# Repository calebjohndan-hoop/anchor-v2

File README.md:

# ANCHOR v2

**A two-ear noise cancelling earmuff for factory and construction workers that cancels machine noise but lets alarms and voices through.**

Status: design stage. v2 has not been built yet.

## What it is

ANCHOR is an industrial earmuff with active noise cancelling and a small on-device sound classifier. Microphones outside each cup hear the machine noise, and an ESP32-S3 plays anti-noise through a speaker inside the cup. When the classifier hears an alarm or a voice, ANCHOR stops cancelling and plays the outside sound into the ear instead.

## Why I'm making it

Earmuffs protect hearing but block everything, including reversing alarms, fire alarms and a supervisor shouting a warning. Many workers take them off to stay aware, which is when hearing gets damaged. Smart hearing protection that solves this exists, but it is expensive and imported. I want a low cost version that a factory in India could actually buy.

I already built a rough v1 (about ₹2,200) for a college design thinking course with my teammates. It proved the idea: noise cancelling works on steady machine hum, and the mic to speaker delay was 3.5 to 4.5 ms. But it was a breadboard with about 30 loose wires on the headband, one ear only, and ran from a power bank. v2 is a proper redesign. See [v1/README.md](v1/README.md).

## What changes in v2

| | v1 (built) | v2 (planned) |
|---|---|---|
| Ears with cancelling | 1 | 2 |
| Electronics | Breadboard on the headband | Custom PCBs inside the cups |
| Wiring | About 30 jumper wires | One 8-wire cable, digital signals only |
| Power | USB power bank | 1000 mAh LiPo, USB-C charging |
| Mic to speaker delay | 3.5 to 4.5 ms (measured) | Under 1 ms (target) |
| Noise reduction | Not measured | Measured with a sound level meter |

## Firmware and AI

v2 keeps the v1 firmware and the trained sound classifier. Each ear is wired exactly like v1 on its own I2S port (left ear on the v1 pins), so v1 sketches run on the left ear unchanged, and [firmware/v2/11_anchor_v2](firmware/v2/11_anchor_v2) runs the v1 cancelling engine in both ears with the same AI. It compiles and links for the ESP32-S3 with both the built-in AI and the Edge Impulse model; it has not run on v2 hardware yet. The ICS-43434 mics have the same -26 dBFS sensitivity and 24-bit I2S format as v1's INMP441, so the training clips still match.

## Design

Full plan: [docs/DESIGN.md](docs/DESIGN.md)

### Wiring

### Schematic and PCB

Three KiCad 7 boards: the main board (51 x 38 mm, left cup), a mic board (12 x 13 mm, four needed) and a right cup hub (30 x 22 mm). Schematics, layouts, Gerbers and JLCPCB BOM and position files are in [pcb/](pcb/).

**Status:** routed and DRC clean (no clearance, unconnected or courtyard errors), but this is a first revision that has **not been reviewed by a second person or built**. See [pcb/README.md](pcb/README.md) for the checks to do before ordering.

### 3D model

Enclosure parts are parametric CadQuery models ([cad/anchor_cad.py](cad/anchor_cad.py)) with STEP files, also imported into [Onshape](https://cad.onshape.com/documents/01ac43861da2c203e8e859be). Cup sizes are placeholders until the earmuff is measured.

## Repo layout

| Folder | Contents |
|---|---|
| `docs/` | Design plan and diagrams |
| `pcb/` | KiCad projects: main board, mic board, right hub |
| `cad/` | Onshape link and exported STEP and STL files |
| `firmware/` | ESP32-S3 Arduino code |
| `v1/` | Photos and notes from the first prototype |

## Credits

v1 was built with my college teammates. I used Claude (an AI assistant) to write this v2 design plan, generate the CAD models and lay out the PCBs. I am reviewing them before anything is ordered.

## Bill of materials

Everything comes in two online orders, delivered: one JLCPCB order (boards fully assembled, chips, and the 3D printed parts) and one Amazon.in order (earmuff, battery, speakers, cables, fixings, tools). Prices are estimates without shipping and will be replaced with the real cart prices before review. Full list with notes: [BOM.csv](BOM.csv).

| Part | Qty | Unit (USD) | Total (USD) | Vendor | Funding |
|---|---|---|---|---|---|
| [PCB fabrication: main, hub, mic boards](https://jlcpcb.com/) | 1 | 10.00 | 10.00 | JLCPCB | Requested |
| [PCB assembly (4 jobs: main, hub, mic REF, mic ERR)](https://jlcpcb.com/) | 1 | 70.00 | 70.00 | JLCPCB | Requested |
| [ESP32-S3-WROOM-1-N16R8 module](https://www.lcsc.com/product-detail/C2913202.html) | 2 | 5.50 | 11.00 | JLCPCB | Requested |
| [MAX98357AETE+T I2S class D amplifier](https://www.lcsc.com/product-image/C910544.html) | 4 | 2.00 | 8.00 | JLCPCB | Requested |
| [ICS-43434 I2S MEMS microphone](https://www.lcsc.com/product-detail/C5656610.html) | 10 | 2.50 | 25.00 | JLCPCB | Requested |
| [MCP73831T-2ACI/OT LiPo charger IC](https://www.lcsc.com/search?q=MCP73831T-2ACI%2FOT) | 2 | 0.60 | 1.20 | JLCPCB | Requested |
| [AP2112K-3.3 LDO regulator](https://www.lcsc.com/search?q=AP2112K-3.3TRG1) | 2 | 0.20 | 0.40 | JLCPCB | Requested |
| [USBLC6-2SC6 USB ESD protection](https://www.lcsc.com/search?q=USBLC6-2SC6) | 2 | 0.20 | 0.40 | JLCPCB | Requested |
| [USB-C 16-pin receptacle](https://www.lcsc.com/search?q=TYPE-C%2016PIN) | 2 | 0.30 | 0.60 | JLCPCB | Requested |
| [AO3401A P-MOSFETs + SS14 Schottky](https://www.lcsc.com/search?q=AO3401A) | 4 | 0.20 | 0.80 | JLCPCB | Requested |
| [JST-SH and JST-PH SMD connectors](https://www.lcsc.com/search?q=SM05B-SRSS-TB) | 28 | 0.15 | 4.20 | JLCPCB | Requested |
| [Passives lot (resistors, capacitors, ferrite bead)](https://www.lcsc.com/search?q=0603%20resistor) | 1 | 4.00 | 4.00 | JLCPCB | Requested |
| [Buttons, slide switch, LEDs](https://www.lcsc.com/search?q=tactile%20switch) | 1 | 2.00 | 2.00 | JLCPCB | Requested |
| [3D printed enclosure parts (JLC3DP, resin)](https://jlc3dp.com/) | 1 | 30.00 | 30.00 | JLCPCB | Requested |
| [Industrial safety earmuff (same model as v1)](https://www.amazon.in/s?k=industrial+safety+earmuff+red) | 1 | 5.00 | 5.00 | Amazon.in | Requested |
| [3.7 V 1000 mAh LiPo (503450) with JST-PH plug](https://www.amazon.in/s?k=3.7v+1000mah+lipo+battery+503450+jst+ph) | 2 | 5.00 | 10.00 | Amazon.in | Requested |
| [40 mm 32 ohm headphone driver](https://www.amazon.in/s?k=40mm+32+ohm+headphone+driver) | 4 | 4.00 | 16.00 | Amazon.in | Requested |
| [JST-SH 1.0 mm double-ended cables (2, 5 and 8 pin)](https://www.amazon.in/s?k=JST+SH+1.0mm+double+ended+cable) | 1 | 8.00 | 8.00 | Amazon.in | Requested |
| [M2 screw assortment](https://www.amazon.in/s?k=M2+screw+assortment+kit) | 1 | 4.00 | 4.00 | Amazon.in | Requested |
| [Acoustic foam sheet](https://www.amazon.in/s?k=acoustic+foam+sheet+thin) | 1 | 4.00 | 4.00 | Amazon.in | Requested |
| [Double-sided foam tape](https://www.amazon.in/s?k=double+sided+foam+tape) | 1 | 3.00 | 3.00 | Amazon.in | Requested |
| [Heat shrink and spiral cable wrap](https://www.amazon.in/s?k=heat+shrink+tube+kit) | 1 | 4.00 | 4.00 | Amazon.in | Requested |
| [UNI-T UT353 sound level meter](https://www.amazon.in/s?k=UNI-T+UT353+sound+level+meter) | 1 | 27.00 | 27.00 | Amazon.in | Requested |
| [Soldering iron kit with multimeter, solder and flux](https://www.amazon.in/s?k=soldering+iron+kit+with+multimeter) | 1 | 27.00 | 27.00 | Amazon.in | Requested |
| **Total** |  |  | **275.60** |  |  |
| **Grant total** |  |  | **275.60** |  |  |

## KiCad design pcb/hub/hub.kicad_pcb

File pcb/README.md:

# PCBs (KiCad 7)

| Board | Size | Qty | Folder |
|---|---|---|---|
| Main board (left cup): ESP32-S3-WROOM-1-N16R8, left MAX98357A, MCP73831 charger, AP2112K-3.3, USB-C | 51 x 38 mm | 1 per headset | [main/](main/) |
| Mic board: ICS-43434, JST-SH 5, sound port hole; REF and ERR builds | 12 x 13 mm | 2 REF + 2 ERR per headset | [mic/](mic/) |
| Right cup hub: right MAX98357A, 8-pin cable in, 2 mic sockets, speaker socket | 30 x 22 mm | 1 per headset | [hub/](hub/) |

Each folder has the schematic (`.kicad_sch`, plus a PDF), the board (`.kicad_pcb`), the DRC report, front and back images, and `fab/` with Gerbers, drill files, `positions.csv` and `bom-jlcpcb.csv` for assembly.

## How these were made

The boards are generated from code in [gen/](gen/): `boards.py` lists every part and connection, `place.py` sets the placement, and `run_all.py` builds the schematics and boards, routes them with Freerouting, adds ground pours, runs DRC and exports the fab files. KiCad reads the schematics back and the script checks every net matches the parts list.

Schematics are drawn with net labels (parts joined by labels with the same name) rather than wires.

## DRC status

All three boards: no clearance, unconnected, short or courtyard errors. Remaining items are silkscreen text overlaps (cosmetic) and "footprint not in project library" notices, because the boards use KiCad's standard libraries.

## Design notes

- **Radio is not used.** The ESP32-S3 antenna keepout and its large courtyard were removed so parts and ground pour can sit near the module. If Wi-Fi or Bluetooth is ever needed, the board must be re-laid out with the keepout back.
- **Mic boards: one PCB, two builds.** The REF build fits R1 (L/R to GND, left slot) and the ERR build fits R2 (L/R to 3.3 V, right slot), exactly like v1's INMP441 wiring. Order the mic PCB twice at JLCPCB, once with `fab/bom-jlcpcb-REF.csv` and once with `fab/bom-jlcpcb-ERR.csv`. Nothing to bridge by hand.
- **Mic GND ring:** the ICS-43434 GND pad is a ring around the sound port; a short trace was added by hand because the autorouter skips that pad shape. Loose copper rings in the library footprint were removed.
- **Charge status:** MCP73831 STAT swings to 5 V, so it reaches GPIO 2 through a 10k/20k divider.
- **Each ear is its own I2S port, wired like v1:** left on GPIO 5, 6, 7, 15 (v1 pins), right on GPIO 17, 18, 21, 16. Both amps get SD_MODE through 10 kΩ from GPIO 8, which has a 10 kΩ pull-up, so the amps are on by default and v1 firmware works without changes. The firmware writes the same sound to both slots, as in v1.
- **Speakers** connect with 2-pin JST-SH, the battery with 2-pin JST-PH (most LiPo packs come with PH).
- **Right amp on the hub:** the headband cable carries only the right ear's digital I2S port (pin 1 to 8: 3V3, GND, BCLK, WS, DIN, GND, DOUT, AMP_SD). Class D speaker outputs never run beside the mic lines. The hub amp runs from 3.3 V through a ferrite bead.
- **Reverse battery protection:** AO3401A P-MOSFET in the battery line (gate to GND).
- **Power switch** drives only the regulator EN pin (100 kΩ pull-down), so its 300 mA rating is not an issue.
- **Cable:** the 8-pin JST-SH cable must be wired pin 1 to pin 1. Pre-made SH cables are sold both straight and reversed; check before plugging in.

## Check before ordering

This is an autorouted first revision and has not been built.

- [ ] Open each board in KiCad 7 or 8 and run DRC and ERC yourself
- [ ] Check the ICS-43434 footprint and sound port against the TDK datasheet
- [ ] Check the MAX98357A SD_MODE voltage window for "left/both" (about 2.5 V here) in the datasheet
- [ ] Look over the autorouted traces and add GND stitching vias if the pours look broken up
- [ ] Run ERC in KiCad (the command-line KiCad 7 used here cannot)
- [ ] Check the battery's plug polarity matches J2 (pin 1 = +) before connecting; the MOSFET protects against a reversed pack, but check anyway
- [ ] Confirm every part in `bom-jlcpcb.csv` is in stock at JLCPCB, then fill in the LCSC part numbers
- [ ] Measure the earmuff and confirm the board outlines fit the cup trays in [../cad/](../cad/)

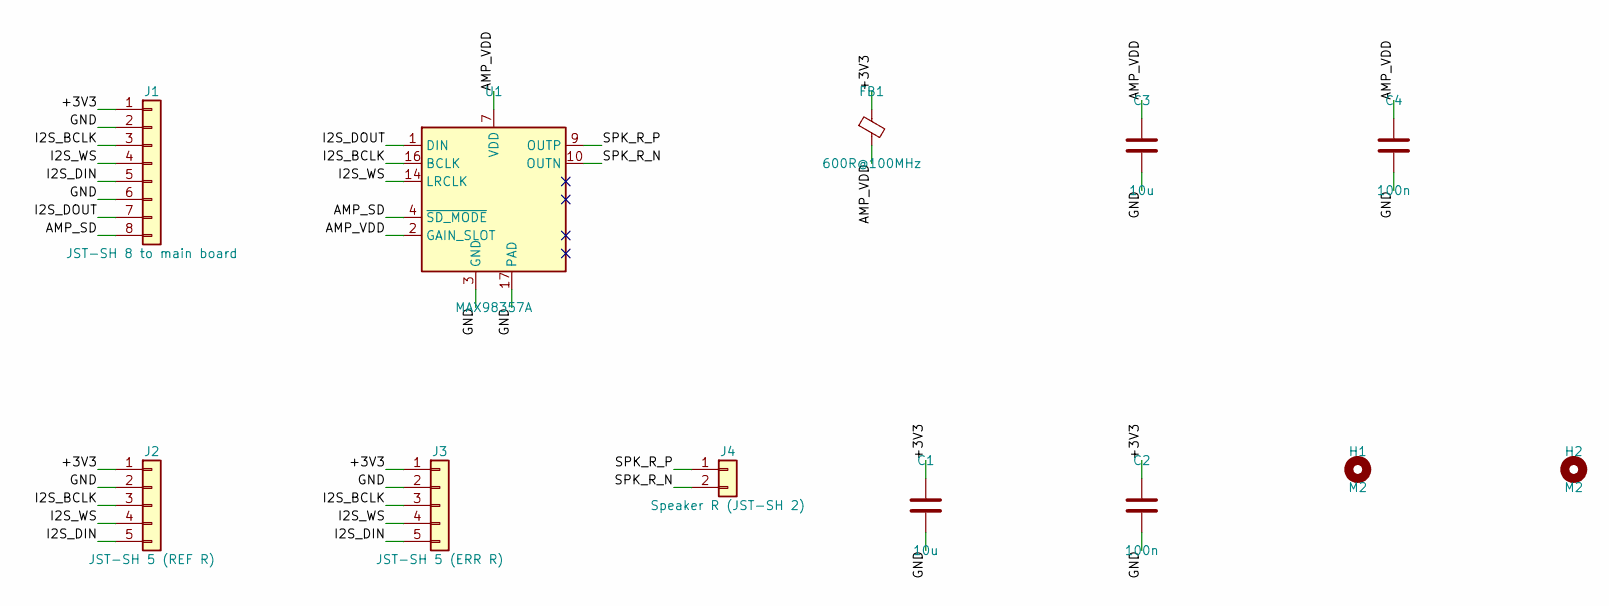
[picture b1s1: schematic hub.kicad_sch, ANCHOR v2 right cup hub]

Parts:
C1, C3: 10u; C_0805_2012Metric
C2, C4: 100n; C_0603_1608Metric
FB1: 600R@100MHz; L_0603_1608Metric
H1, H2: M2; MountingHole_2.2mm_M2
J1: JST-SH 8 to main board; JST_SH_SM08B-SRSS-TB_1x08-1MP_P1.00mm_Horizontal; MPN SM08B-SRSS-TB
J2: JST-SH 5 (REF R); JST_SH_SM05B-SRSS-TB_1x05-1MP_P1.00mm_Horizontal; MPN SM05B-SRSS-TB
J3: JST-SH 5 (ERR R); JST_SH_SM05B-SRSS-TB_1x05-1MP_P1.00mm_Horizontal; MPN SM05B-SRSS-TB
J4: Speaker R (JST-SH 2); JST_SH_SM02B-SRSS-TB_1x02-1MP_P1.00mm_Horizontal; MPN SM02B-SRSS-TB
U1: MAX98357A; TQFN-16-1EP_3x3mm_P0.5mm_EP1.23x1.23mm; MPN MAX98357AETE+T; LCSC C910544

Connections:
+3V3: C1.1, C2.1, FB1.1, J1.1, J2.1, J3.1
AMP_SD: J1.8, U1.4 (~SD_MODE)
AMP_VDD: C3.1, C4.1, FB1.2, U1.2 (GAIN_SLOT), U1.7 (VDD), U1.8 (VDD)
GND: C1.2, C2.2, C3.2, C4.2, J1.2, J1.6, J2.2, J3.2, U1.3 (GND), U1.11 (GND), U1.15 (GND), U1.17 (PAD)
I2S_BCLK: J1.3, J2.3, J3.3, U1.16 (BCLK)
I2S_DIN: J1.5, J2.5, J3.5
I2S_DOUT: J1.7, U1.1 (DIN)
I2S_WS: J1.4, J2.4, J3.4, U1.14 (LRCLK)
SPK_R_N: J4.2, U1.10 (OUTN)
SPK_R_P: J4.1, U1.9 (OUTP)

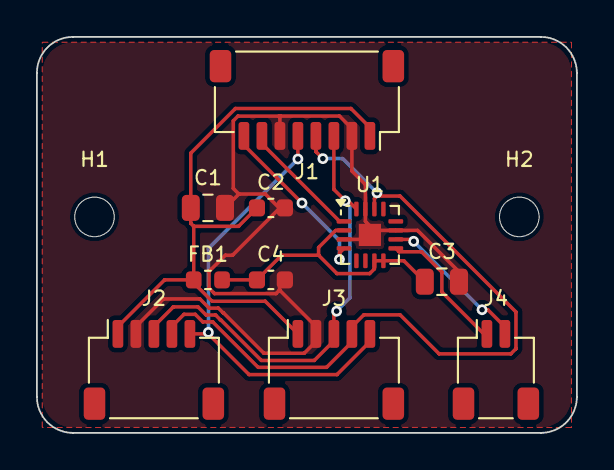
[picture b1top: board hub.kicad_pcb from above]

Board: 2 copper layers, 30.0 x 22.0 mm, 12 parts (0 on the bottom side), 10 nets.

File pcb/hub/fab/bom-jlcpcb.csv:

Comment,Designator,Footprint,LCSC Part #,MPN
10u,"C3,C1",C_0805_2012Metric,,
100n,"C4,C2",C_0603_1608Metric,,
600R@100MHz,FB1,L_0603_1608Metric,,
JST-SH 8 to main board,J1,JST_SH_SM08B-SRSS-TB_1x08-1MP_P1.00mm_Horizontal,,SM08B-SRSS-TB
JST-SH 5 (REF R),J2,JST_SH_SM05B-SRSS-TB_1x05-1MP_P1.00mm_Horizontal,,SM05B-SRSS-TB
JST-SH 5 (ERR R),J3,JST_SH_SM05B-SRSS-TB_1x05-1MP_P1.00mm_Horizontal,,SM05B-SRSS-TB
Speaker R (JST-SH 2),J4,JST_SH_SM02B-SRSS-TB_1x02-1MP_P1.00mm_Horizontal,,SM02B-SRSS-TB
MAX98357A,U1,TQFN-16-1EP_3x3mm_P0.5mm_EP1.23x1.23mm,C910544,MAX98357AETE+T

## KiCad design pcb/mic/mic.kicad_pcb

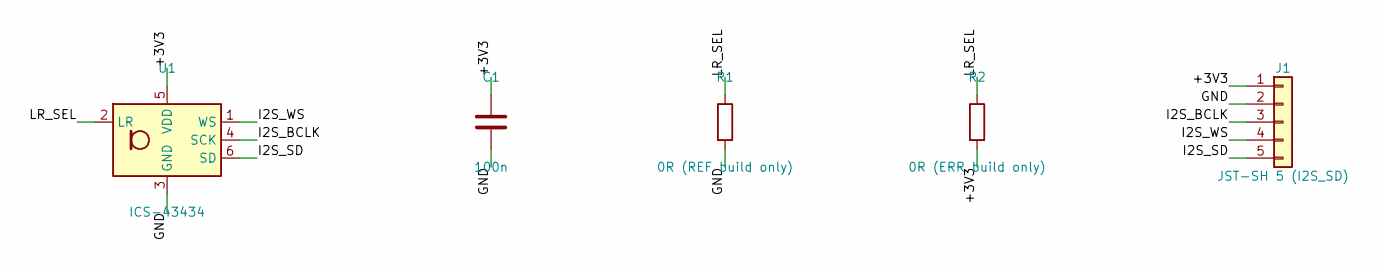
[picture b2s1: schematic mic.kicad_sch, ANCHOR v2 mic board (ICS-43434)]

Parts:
C1: 100n; C_0603_1608Metric
J1: JST-SH 5 (I2S_SD); JST_SH_SM05B-SRSS-TB_1x05-1MP_P1.00mm_Horizontal; MPN SM05B-SRSS-TB
R1: 0R (REF build only); R_0603_1608Metric
R2: 0R (ERR build only); R_0603_1608Metric
U1: ICS-43434; InvenSense_ICS-43434-6_3.5x2.65mm; MPN ICS-43434; LCSC C5656610

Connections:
+3V3: C1.1, J1.1, R2.2, U1.5 (VDD)
GND: C1.2, J1.2, R1.2, U1.3 (GND)
I2S_BCLK: J1.3, U1.4 (SCK)
I2S_SD: J1.5, U1.6 (SD)
I2S_WS: J1.4, U1.1 (WS)
LR_SEL: R1.1, R2.1, U1.2 (LR)

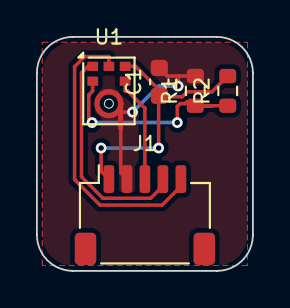
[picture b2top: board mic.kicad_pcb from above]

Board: 2 copper layers, 12.0 x 13.0 mm, 5 parts (0 on the bottom side), 6 nets.

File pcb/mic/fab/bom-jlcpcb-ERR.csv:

Comment,Designator,Footprint,LCSC Part #,MPN
100n,C1,C_0603_1608Metric,,
JST-SH 5 (I2S_SD),J1,JST_SH_SM05B-SRSS-TB_1x05-1MP_P1.00mm_Horizontal,,SM05B-SRSS-TB
0R,R2,R_0603_1608Metric,,
ICS-43434,U1,InvenSense_ICS-43434-6_3.5x2.65mm,C5656610,ICS-43434

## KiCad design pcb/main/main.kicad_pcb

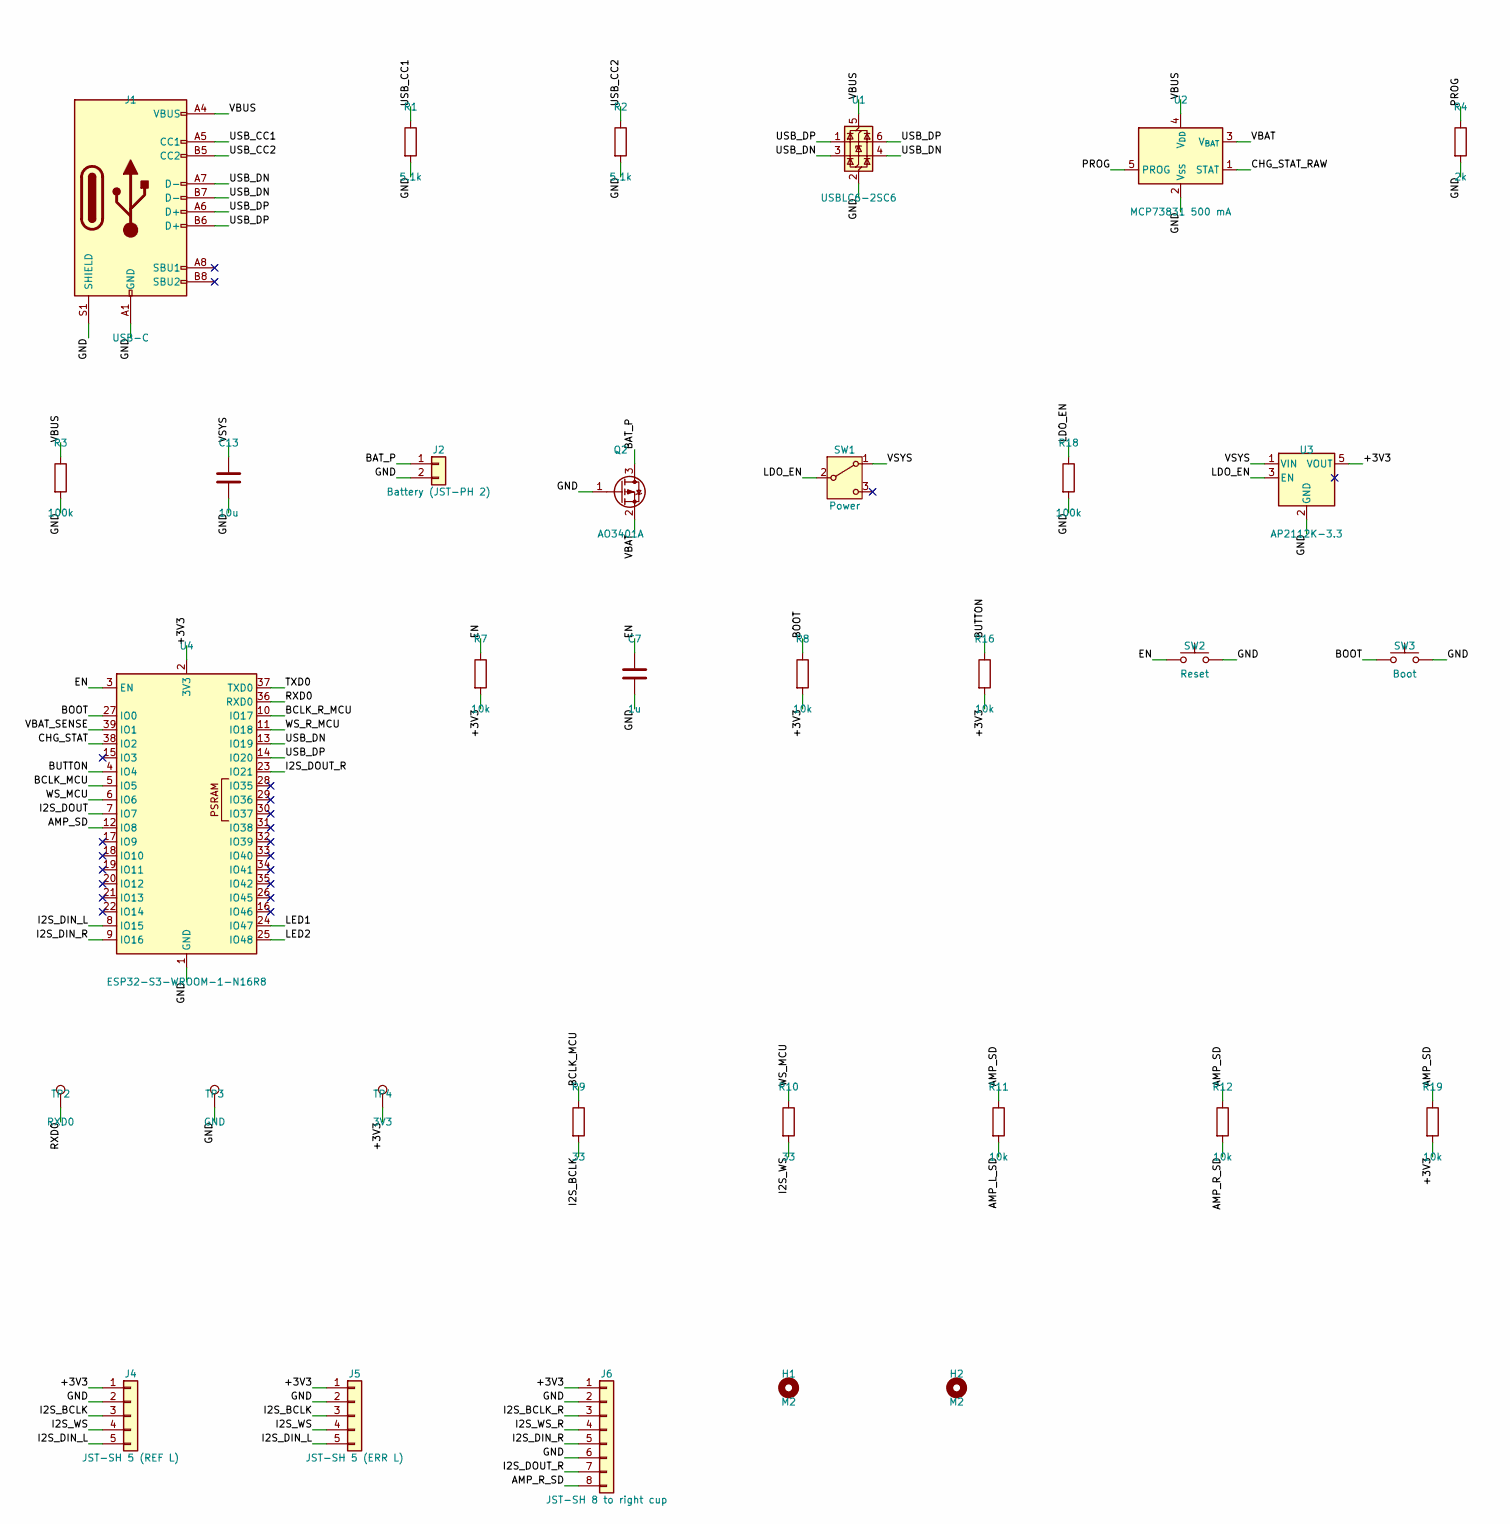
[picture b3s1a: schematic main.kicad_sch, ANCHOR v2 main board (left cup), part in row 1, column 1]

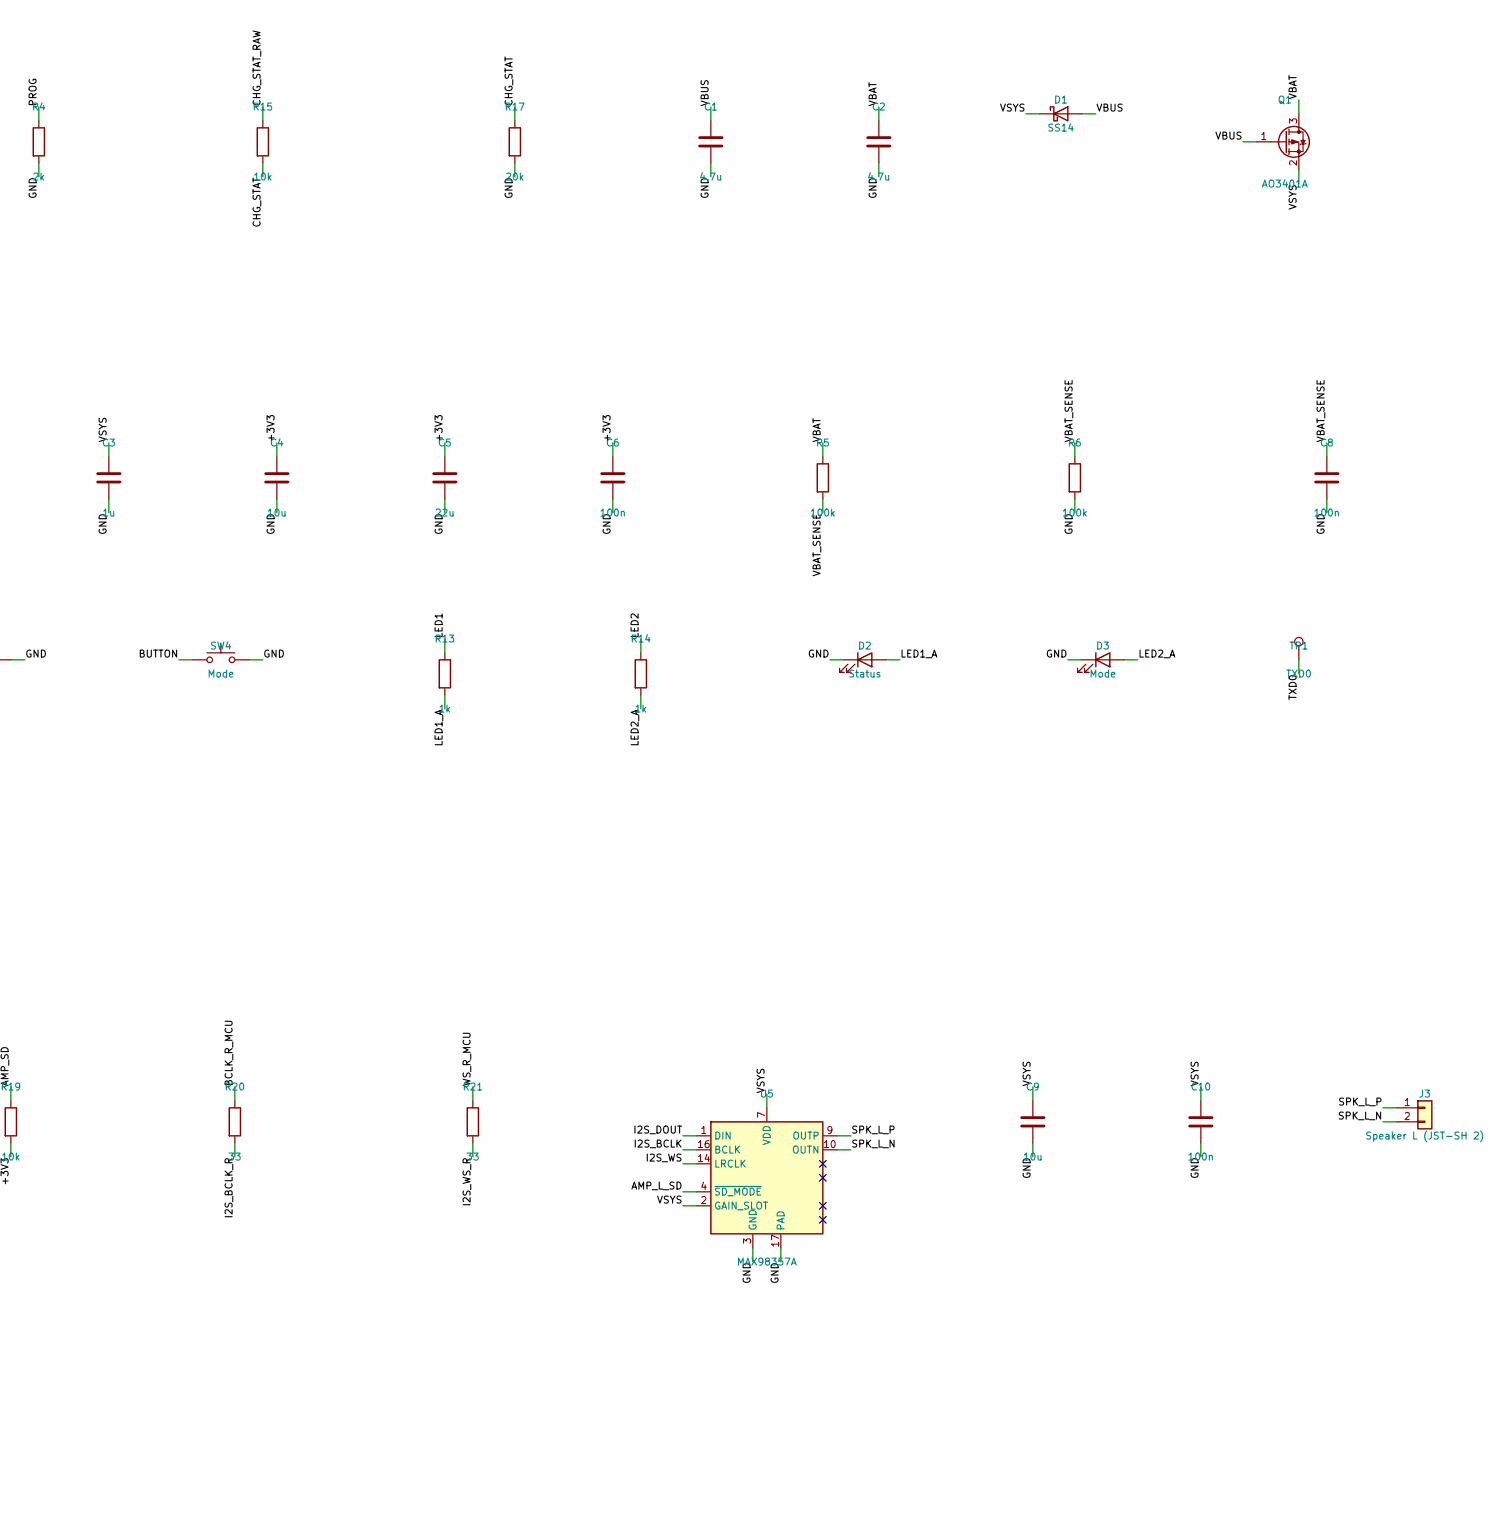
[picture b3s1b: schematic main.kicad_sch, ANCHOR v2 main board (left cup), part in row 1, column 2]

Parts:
C1, C2: 4.7u; C_0603_1608Metric
C3, C7: 1u; C_0603_1608Metric
C4, C9, C13: 10u; C_0805_2012Metric
C5: 22u; C_0805_2012Metric
C6, C8, C10: 100n; C_0603_1608Metric
D1: SS14; D_SMA; MPN SS14
D2: Status; LED_0603_1608Metric
D3: Mode; LED_0603_1608Metric
H1, H2: M2; MountingHole_2.2mm_M2
J1: USB-C; USB_C_Receptacle_HRO_TYPE-C-31-M-12; MPN TYPE-C-31-M-12
J2: Battery (JST-PH 2); JST_PH_S2B-PH-SM4-TB_1x02-1MP_P2.00mm_Horizontal; MPN S2B-PH-SM4-TB
J3: Speaker L (JST-SH 2); JST_SH_SM02B-SRSS-TB_1x02-1MP_P1.00mm_Horizontal; MPN SM02B-SRSS-TB
J4: JST-SH 5 (REF L); JST_SH_SM05B-SRSS-TB_1x05-1MP_P1.00mm_Horizontal; MPN SM05B-SRSS-TB
J5: JST-SH 5 (ERR L); JST_SH_SM05B-SRSS-TB_1x05-1MP_P1.00mm_Horizontal; MPN SM05B-SRSS-TB
J6: JST-SH 8 to right cup; JST_SH_SM08B-SRSS-TB_1x08-1MP_P1.00mm_Horizontal; MPN SM08B-SRSS-TB
Q1, Q2: AO3401A; SOT-23; MPN AO3401A
R1, R2: 5.1k; R_0603_1608Metric
R3, R5, R6, R18: 100k; R_0603_1608Metric
R4: 2k; R_0603_1608Metric
R7, R8, R11, R12, R15, R16, R19: 10k; R_0603_1608Metric
R9, R10, R20, R21: 33; R_0603_1608Metric
R13, R14: 1k; R_0603_1608Metric
R17: 20k; R_0603_1608Metric
SW1: Power; SW_SPDT_PCM12; MPN PCM12SMTR
SW2: Reset; SW_Push_1P1T_NO_CK_KMR2
SW3: Boot; SW_Push_1P1T_NO_CK_KMR2
SW4: Mode; SW_Push_1P1T_NO_CK_KMR2
TP1: TXD0; TestPoint_Pad_D1.0mm
TP2: RXD0; TestPoint_Pad_D1.0mm
TP3: GND; TestPoint_Pad_D1.0mm
TP4: 3V3; TestPoint_Pad_D1.0mm
U1: USBLC6-2SC6; SOT-23-6; MPN USBLC6-2SC6
U2: MCP73831 500 mA; SOT-23-5; MPN MCP73831T-2ACI/OT
U3: AP2112K-3.3; SOT-23-5; MPN AP2112K-3.3TRG1
U4: ESP32-S3-WROOM-1-N16R8; ESP32-S3-WROOM-1; MPN ESP32-S3-WROOM-1-N16R8; LCSC C2913202
U5: MAX98357A; TQFN-16-1EP_3x3mm_P0.5mm_EP1.23x1.23mm; MPN MAX98357AETE+T; LCSC C910544

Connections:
+3V3: C4.1, C5.1, C6.1, J4.1, J5.1, J6.1, R7.2, R8.2, R16.2, R19.2, TP4.1, U3.5 (VOUT), U4.2 (3V3)
AMP_L_SD: R11.2, U5.4 (~SD_MODE)
AMP_R_SD: J6.8, R12.2
AMP_SD: R11.1, R12.1, R19.1, U4.12 (IO8)
BAT_P: J2.1, Q2.3 (D)
BCLK_MCU: R9.1, U4.5 (IO5)
BCLK_R_MCU: R20.1, U4.10 (IO17)
BOOT: R8.1, SW3.1, U4.27 (IO0)
BUTTON: R16.1, SW4.1, U4.4 (IO4)
CHG_STAT: R15.2, R17.1, U4.38 (IO2)
CHG_STAT_RAW: R15.1, U2.1 (STAT)
EN: C7.1, R7.1, SW2.1, U4.3 (EN)
GND: C1.2, C2.2, C3.2, C4.2, C5.2, C6.2, C7.2, C8.2, C9.2, C10.2, C13.2, D2.1 (K), D3.1 (K), J1.A1 (GND), J1.A12 (GND), J1.B1 (GND), J1.B12 (GND), J1.S1 (SHIELD), J2.2, J4.2, J5.2, J6.2, J6.6, Q2.1 (G), R1.2, R2.2, R3.2, R4.2, R6.2, R17.2, R18.2, SW2.2, SW3.2, SW4.2, TP3.1, U1.2 (GND), U2.2 (V_{SS}), U3.2 (GND), U4.1 (GND), U4.40 (GND), U4.41 (GND), U5.3 (GND), U5.11 (GND), U5.15 (GND), U5.17 (PAD)
I2S_BCLK: J4.3, J5.3, R9.2, U5.16 (BCLK)
I2S_BCLK_R: J6.3, R20.2
I2S_DIN_L: J4.5, J5.5, U4.8 (IO15)
I2S_DIN_R: J6.5, U4.9 (IO16)
I2S_DOUT: U4.7 (IO7), U5.1 (DIN)
I2S_DOUT_R: J6.7, U4.23 (IO21)
I2S_WS: J4.4, J5.4, R10.2, U5.14 (LRCLK)
I2S_WS_R: J6.4, R21.2
LDO_EN: R18.1, SW1.2 (B), U3.3 (EN)
LED1: R13.1, U4.24 (IO47)
LED1_A: D2.2 (A), R13.2
LED2: R14.1, U4.25 (IO48)
LED2_A: D3.2 (A), R14.2
PROG: R4.1, U2.5 (PROG)
RXD0: TP2.1, U4.36 (RXD0)
SPK_L_N: J3.2, U5.10 (OUTN)
SPK_L_P: J3.1, U5.9 (OUTP)
TXD0: TP1.1, U4.37 (TXD0)
USB_CC1: J1.A5 (CC1), R1.1
USB_CC2: J1.B5 (CC2), R2.1
USB_DN: J1.A7 (D-), J1.B7 (D-), U1.3 (I/O2), U1.4 (I/O2), U4.13 (IO19)
USB_DP: J1.A6 (D+), J1.B6 (D+), U1.1 (I/O1), U1.6 (I/O1), U4.14 (IO20)
VBAT: C2.1, Q1.3 (D), Q2.2 (S), R5.1, U2.3 (V_{BAT})
VBAT_SENSE: C8.1, R5.2, R6.1, U4.39 (IO1)
VBUS: C1.1, D1.2 (A), J1.A4 (VBUS), J1.A9 (VBUS), J1.B4 (VBUS), J1.B9 (VBUS), Q1.1 (G), R3.1, U1.5 (VBUS), U2.4 (V_{DD})
VSYS: C3.1, C9.1, C10.1, C13.1, D1.1 (K), Q1.2 (S), SW1.1 (A), U3.1 (VIN), U5.2 (GAIN_SLOT), U5.7 (VDD), U5.8 (VDD)
WS_MCU: R10.1, U4.6 (IO6)
WS_R_MCU: R21.1, U4.11 (IO18)

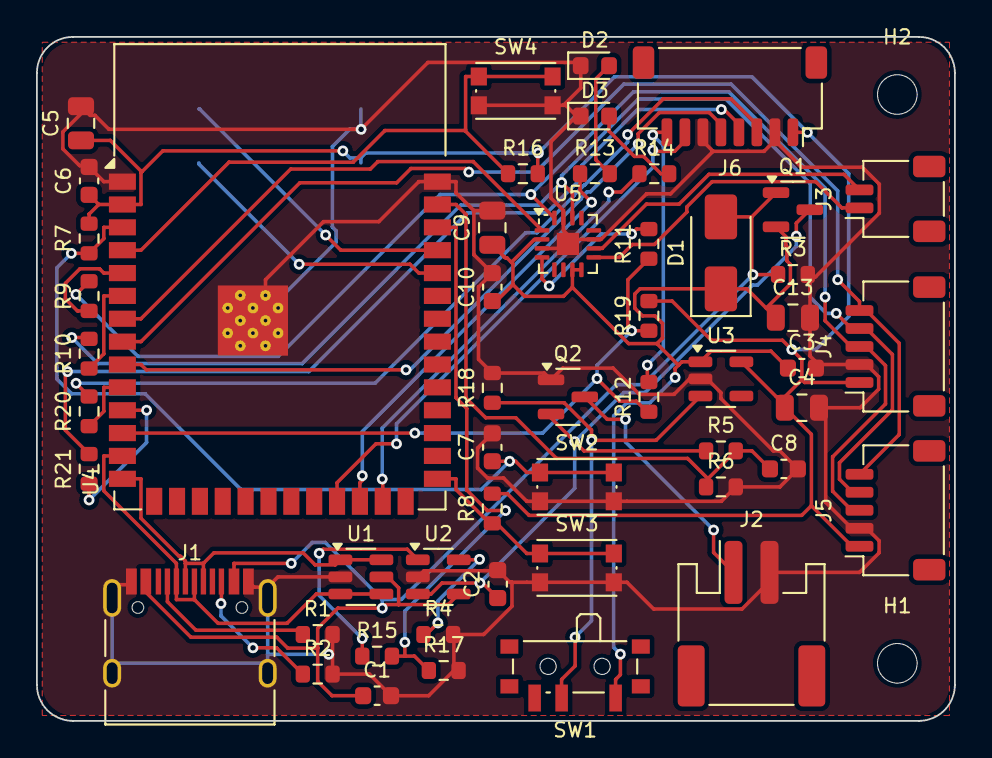
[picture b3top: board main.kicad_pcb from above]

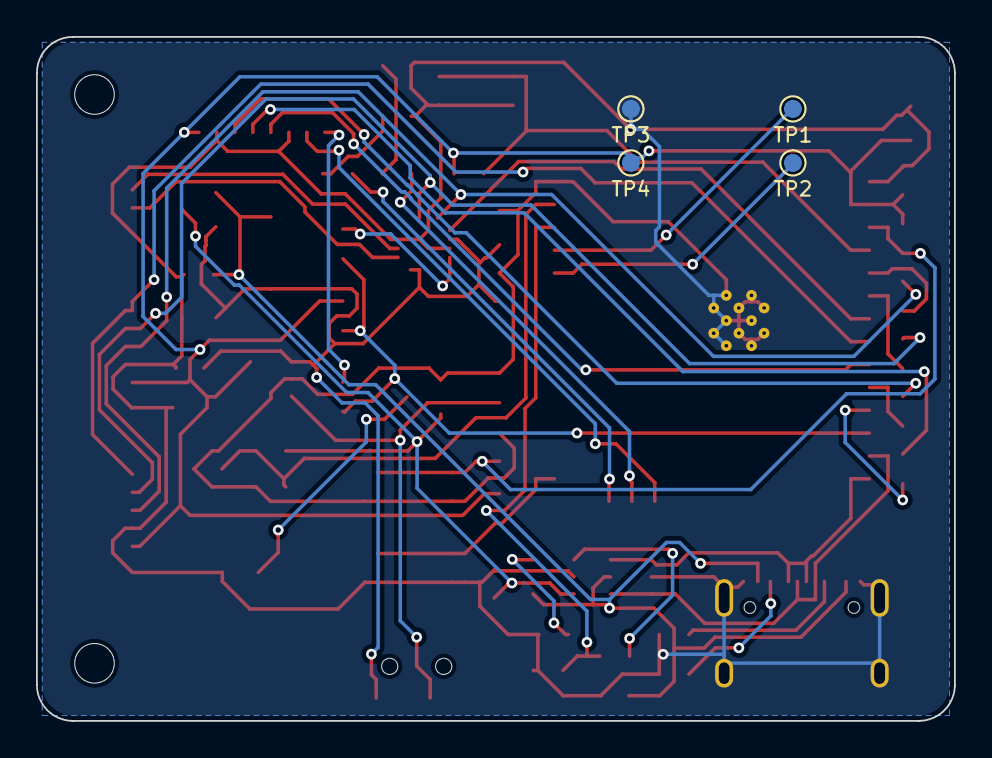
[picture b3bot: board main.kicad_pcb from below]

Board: 2 copper layers, 51.0 x 38.0 mm, 58 parts (4 on the bottom side), 41 nets.

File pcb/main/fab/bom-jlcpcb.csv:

Comment,Designator,Footprint,LCSC Part #,MPN
4.7u,"C1,C2",C_0603_1608Metric,,
10u,"C13,C4,C9",C_0805_2012Metric,,
1u,"C3,C7",C_0603_1608Metric,,
22u,C5,C_0805_2012Metric,,
100n,"C6,C8,C10",C_0603_1608Metric,,
SS14,D1,D_SMA,,SS14
Status,D2,LED_0603_1608Metric,,
Mode,D3,LED_0603_1608Metric,,
USB-C,J1,USB_C_Receptacle_HRO_TYPE-C-31-M-12,,TYPE-C-31-M-12
Battery (JST-PH 2),J2,JST_PH_S2B-PH-SM4-TB_1x02-1MP_P2.00mm_Horizontal,,S2B-PH-SM4-TB
Speaker L (JST-SH 2),J3,JST_SH_SM02B-SRSS-TB_1x02-1MP_P1.00mm_Horizontal,,SM02B-SRSS-TB
JST-SH 5 (REF L),J4,JST_SH_SM05B-SRSS-TB_1x05-1MP_P1.00mm_Horizontal,,SM05B-SRSS-TB
JST-SH 5 (ERR L),J5,JST_SH_SM05B-SRSS-TB_1x05-1MP_P1.00mm_Horizontal,,SM05B-SRSS-TB
JST-SH 8 to right cup,J6,JST_SH_SM08B-SRSS-TB_1x08-1MP_P1.00mm_Horizontal,,SM08B-SRSS-TB
AO3401A,"Q1,Q2",SOT-23,,AO3401A
5.1k,"R1,R2",R_0603_1608Metric,,
1k,"R13,R14",R_0603_1608Metric,,
10k,"R15,R7,R8,R16,R11,R12,R19",R_0603_1608Metric,,
20k,R17,R_0603_1608Metric,,
100k,"R3,R18,R5,R6",R_0603_1608Metric,,
2k,R4,R_0603_1608Metric,,
33,"R9,R10,R20,R21",R_0603_1608Metric,,
Power,SW1,SW_SPDT_PCM12,,PCM12SMTR
Reset,SW2,SW_Push_1P1T_NO_CK_KMR2,,
Boot,SW3,SW_Push_1P1T_NO_CK_KMR2,,
Mode,SW4,SW_Push_1P1T_NO_CK_KMR2,,
USBLC6-2SC6,U1,SOT-23-6,,USBLC6-2SC6
MCP73831 500 mA,U2,SOT-23-5,,MCP73831T-2ACI/OT
AP2112K-3.3,U3,SOT-23-5,,AP2112K-3.3TRG1
ESP32-S3-WROOM-1-N16R8,U4,ESP32-S3-WROOM-1,C2913202,ESP32-S3-WROOM-1-N16R8
MAX98357A,U5,TQFN-16-1EP_3x3mm_P0.5mm_EP1.23x1.23mm,C910544,MAX98357AETE+T

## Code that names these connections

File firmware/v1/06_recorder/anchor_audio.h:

// =====================================================================
//  ANCHOR - shared audio code (anchor_audio.h)
//  Hardware: ESP32-S3 (N16R8) + 2 x INMP441 digital mics + 1 x MAX98357A amplifier
//  Keep this file in the SAME folder as the .ino sketch that uses it.
//
//  Needs only: ESP32 Arduino core 3.x ("esp32 by Espressif Systems").
//  No extra library, no I2C, no codec settings.
//
//  How it works:
//   ONE I2S port runs both ways at once (full duplex). The ESP32 makes the
//   BCLK and WS clocks; both mics and the MAX98357A listen to the same clocks,
//   so recording and playback always stay in step.
//     - Both mics share one data wire (SD). The mic with L/R = GND talks in
//       the LEFT half of each frame, the mic with L/R = 3.3 V in the RIGHT half.
//     - The MAX98357A gets the speaker sound on its DIN pin and drives the
//       speaker directly (speaker on its two output screws, never to GND).
//       Its SD pin is tied to VIN, so it plays the LEFT channel. We always
//       write the same sound to both channels, so either setting works.
//
//  audioRead() gives stereo 16-bit frames:
//      frame[0] = LEFT  = REF mic (outside, L/R pin to GND)
//      frame[1] = RIGHT = ERR mic (inside,  L/R pin to 3.3 V)
//  audioWrite() takes stereo 16-bit frames for the MAX98357A.
// =====================================================================
#pragma once
#include <Arduino.h>
#include "driver/i2s_std.h"   // part of the ESP32 Arduino core 3.x
#include "driver/gpio.h"

// ---------- Pins: must match the wiring in the build guide ----------
#define PIN_I2S_BCLK  5    // -> SCK of both mics + BCLK of MAX98357A
#define PIN_I2S_WS    6    // -> WS of both mics  + LRCLK of MAX98357A
#define PIN_I2S_DOUT  7    // -> DIN of MAX98357A (sound to the speaker)
#define PIN_I2S_DIN   15   // <- SD of both mics (joined together)

#define SAMPLE_RATE 16000

// If sketch 04 shows the REF and ERR bars the wrong way round, change 0 to 1.
#define SWAP_MIC_CHANNELS 0
#if SWAP_MIC_CHANNELS
  #define CH_REF 1
  #define CH_ERR 0
#else
  #define CH_REF 0
  #define CH_ERR 1
#endif

static i2s_chan_handle_t i2s_tx = nullptr;
static i2s_chan_handle_t i2s_rx = nullptr;

// Software volume (the MAX98357A has only a fixed gain, set by its GAIN pin)
static int32_t anchor_out_gain_q15 = 0;   // speaker gain, 32768 = 1.0
static int32_t anchor_in_gain_q8 = 256;   // mic gain, 256 = 1.0 (0 dB)

// ---------- small helpers ----------
static inline float fromPcm(int16_t s) { return (float)s / 32768.0f; }
static inline int16_t toPcm(float v) {
  if (v > 0.999f) v = 0.999f;
  if (v < -0.999f) v = -0.999f;
  return (int16_t)(v * 32767.0f);
}
static inline int16_t sat16(int32_t v) {
  if (v > 32767) return 32767;
  if (v < -32768) return -32768;
  return (int16_t)v;
}

// Counts how often mic data was lost because the code was too slow.
static volatile uint32_t i2s_rx_overflows = 0;
static bool IRAM_ATTR onRxOverflow(i2s_chan_handle_t h, i2s_event_data_t* e, void* ctx) {
  i2s_rx_overflows = i2s_rx_overflows + 1;
  return false;
}

// Volumes: 0..100, like before.
//   out_volume: speaker loudness, 0 = silent, 100 = full scale.  START LOW (10-20):
//               the MAX98357A is an amplifier and can be LOUD.
//   in_volume : mic gain, 0 = 0 dB ... 100 = +24 dB (done in software).
static void anchorSetVolumes(int out_volume, int in_volume) {
  if (out_volume < 0) out_volume = 0;
  if (out_volume > 100) out_volume = 100;
  if (in_volume < 0) in_volume = 0;
  if (in_volume > 100) in_volume = 100;
  anchor_out_gain_q15 = (int32_t)(out_volume * 32768L / 100);
  anchor_in_gain_q8 = (int32_t)(256.0f * powf(10.0f, (0.24f * in_volume) / 20.0f));
}

// ---------- I2S: the sound wires ----------
// frames_per_dma small (16) = low delay, for noise cancelling
// frames_per_dma big (256)  = never drops samples, for recording
static bool anchorI2SBegin(int frames_per_dma, int dma_count) {
  i2s_chan_config_t chan_cfg = I2S_CHANNEL_DEFAULT_CONFIG(I2S_NUM_0, I2S_ROLE_MASTER);
  chan_cfg.dma_desc_num = dma_count;
  chan_cfg.dma_frame_num = frames_per_dma;
  chan_cfg.auto_clear = true;  // play silence if we are ever late
  if (i2s_new_channel(&chan_cfg, &i2s_tx, &i2s_rx) != ESP_OK) return false;

  // 32-bit slots: the INMP441 sends 24-bit samples inside 32-bit slots.
  // BCLK = 64 x 16 kHz = 1.024 MHz (the INMP441 accepts 0.5 to 3.2 MHz).
  i2s_std_config_t std_cfg = {
    .clk_cfg = I2S_STD_CLK_DEFAULT_CONFIG(SAMPLE_RATE),
    .slot_cfg = I2S_STD_PHILIPS_SLOT_DEFAULT_CONFIG(I2S_DATA_BIT_WIDTH_32BIT, I2S_SLOT_MODE_STEREO),
    .gpio_cfg = {
      .mclk = I2S_GPIO_UNUSED,   // not needed: MAX98357A and INMP441 use only BCLK and WS
      .bclk = (gpio_num_t)PIN_I2S_BCLK,
      .ws = (gpio_num_t)PIN_I2S_WS,
      .dout = (gpio_num_t)PIN_I2S_DOUT,
      .din = (gpio_num_t)PIN_I2S_DIN,
      .invert_flags = { .mclk_inv = false, .bclk_inv = false, .ws_inv = false },
    },
  };

  if (i2s_channel_init_std_mode(i2s_tx, &std_cfg) != ESP_OK) return false;
  if (i2s_channel_init_std_mode(i2s_rx, &std_cfg) != ESP_OK) return false;

  // The two mics take turns on the SD wire. The INMP441 datasheet asks for a
  // pull-down on SD; we use the ESP32's built-in one.
  gpio_pulldown_en((gpio_num_t)PIN_I2S_DIN);

  i2s_event_callbacks_t cbs = {};
  cbs.on_recv_q_ovf = onRxOverflow;
  i2s_channel_register_event_callback(i2s_rx, &cbs, nullptr);

  if (i2s_channel_enable(i2s_tx) != ESP_OK) return false;
  if (i2s_channel_enable(i2s_rx) != ESP_OK) return false;

  // Fill the speaker queue with silence so the delay is always the same
  static int32_t zeros[2 * 256] = {0};
  for (int i = 0; i < dma_count; i++) {
    size_t done = 0;
    int f = frames_per_dma > 256 ? 256 : frames_per_dma;
    i2s_channel_write(i2s_tx, zeros, f * 2 * sizeof(int32_t), &done, 100);
  }
  return true;
}

// Call this once in setup(). Returns false if something failed.
static bool anchorAudioBegin(int out_volume, int in_volume,
                             int frames_per_dma = 16, int dma_count = 3) {
  anchorSetVolumes(out_volume, in_volume);
  if (!anchorI2SBegin(frames_per_dma, dma_count)) {
    Serial.println("ERROR: I2S did not start. Check the board settings (ESP32S3 Dev Module).");
    return false;
  }
  // Throw away the first 50 ms: the INMP441 needs a moment to wake up.
  static int32_t junk[2 * 64];
  size_t got;
  for (int i = 0; i < 13; i++) i2s_channel_read(i2s_rx, junk, sizeof(junk), &got, 100);
  Serial.println("Audio ready (INMP441 mics + MAX98357A).");
  return true;
}

// Read 'frames' stereo frames (L,R,L,R... as int16). Waits until they arrive.
static size_t audioRead(int16_t* buf, size_t frames) {
  static int32_t raw[2 * 128];
  size_t done_frames = 0;
  while (done_frames < frames) {
    size_t want = frames - done_frames;
    if (want > 128) want = 128;
    size_t got = 0;
    i2s_channel_read(i2s_rx, raw, want * 2 * sizeof(int32_t), &got, portMAX_DELAY);
    size_t n = got / (2 * sizeof(int32_t));
    for (size_t i = 0; i < n; i++) {
      // 24-bit sample sits in the top of the 32-bit slot -> 24-bit value -> apply gain -> 16-bit
      int32_t l = raw[2 * i] >> 8;
      int32_t r = raw[2 * i + 1] >> 8;
      buf[2 * (done_frames + i)]     = sat16((int32_t)(((int64_t)l * anchor_in_gain_q8) >> 16));
      buf[2 * (done_frames + i) + 1] = sat16((int32_t)(((int64_t)r * anchor_in_gain_q8) >> 16));
    }
    done_frames += n;
    if (n == 0) break;
  }
  return done_frames;
}

// Write 'frames' stereo frames (int16) to the MAX98357A.
static size_t audioWrite(const int16_t* buf, size_t frames) {
  static int32_t raw[2 * 128];
  size_t done_frames = 0;
  while (done_frames < frames) {
    size_t want = frames - done_frames;
    if (want > 128) want = 128;
    for (size_t i = 0; i < 2 * want; i++) {
      int32_t s = ((int32_t)buf[2 * done_frames + i] * anchor_out_gain_q15) >> 15;  // volume
      raw[i] = s << 16;   // 16-bit sample into the top of the 32-bit slot
    }
    size_t done = 0;
    i2s_channel_write(i2s_tx, raw, want * 2 * sizeof(int32_t), &done, portMAX_DELAY);
    size_t n = done / (2 * sizeof(int32_t));
    done_frames += n;
    if (n == 0) break;
  }
  return done_frames;
}
